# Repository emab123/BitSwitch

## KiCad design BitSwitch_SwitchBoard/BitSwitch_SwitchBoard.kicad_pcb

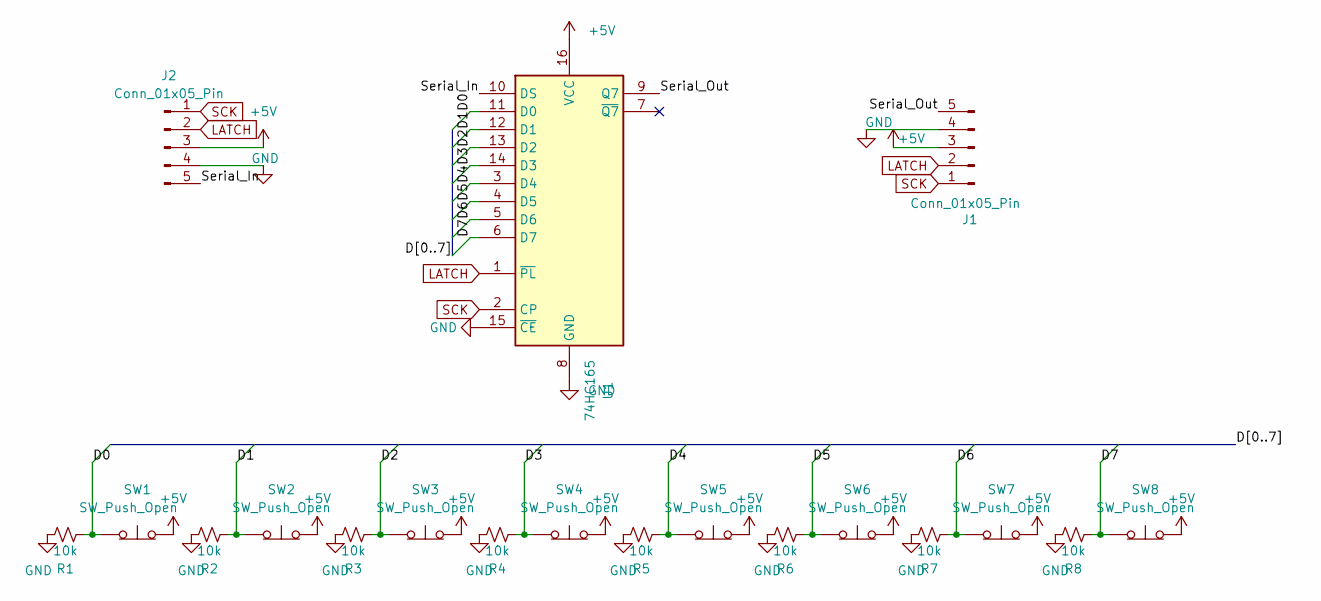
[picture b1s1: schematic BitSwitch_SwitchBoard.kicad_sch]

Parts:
J1, J2: Conn_01x05_Pin; JST_XH_B5B-XH-AM_1x05_P2.50mm_Vertical
R1, R2, R3, R4, R5, R6, R7, R8: 10k; R_0402_1005Metric
SW1, SW2, SW3, SW4, SW5, SW6, SW7, SW8: SW_Push_Open; SW-SMD_HX-KFC-V-105
U1: 74HC165; SOIC-16_3.9x9.9mm_P1.27mm

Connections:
+5V: J1.3, J2.3, SW1.2 (B), SW2.2 (B), SW3.2 (B), SW4.2 (B), SW5.2 (B), SW6.2 (B), SW7.2 (B), SW8.2 (B), U1.16 (VCC)
/D0: R1.2, SW1.1 (A), U1.11 (D0)
/D1: R2.2, SW2.1 (A), U1.12 (D1)
/D2: R3.2, SW3.1 (A), U1.13 (D2)
/D3: R4.2, SW4.1 (A), U1.14 (D3)
/D4: R5.2, SW5.1 (A), U1.3 (D4)
/D5: R6.2, SW6.1 (A), U1.4 (D5)
/D6: R7.2, SW7.1 (A), U1.5 (D6)
/D7: R8.2, SW8.1 (A), U1.6 (D7)
/Serial_In: J2.5, U1.10 (DS)
/Serial_Out: J1.5, U1.9 (Q7)
GND: J1.4, J2.4, R1.1, R2.1, R3.1, R4.1, R5.1, R6.1, R7.1, R8.1, U1.8 (GND), U1.15 (~CE)
LATCH: J1.2, J2.2, U1.1 (~PL)
SCK: J1.1, J2.1, U1.2 (CP)

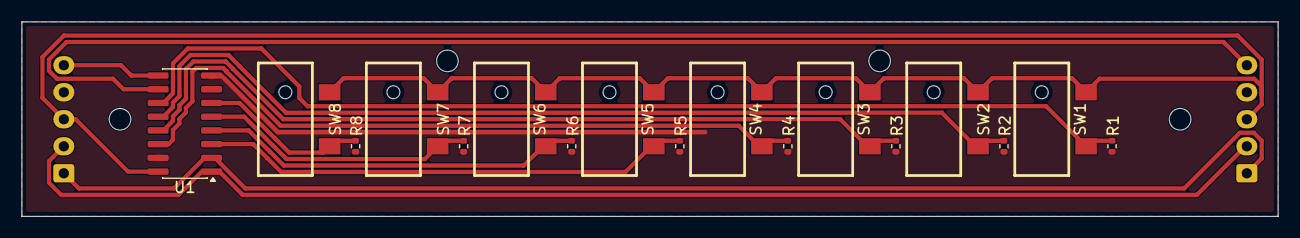
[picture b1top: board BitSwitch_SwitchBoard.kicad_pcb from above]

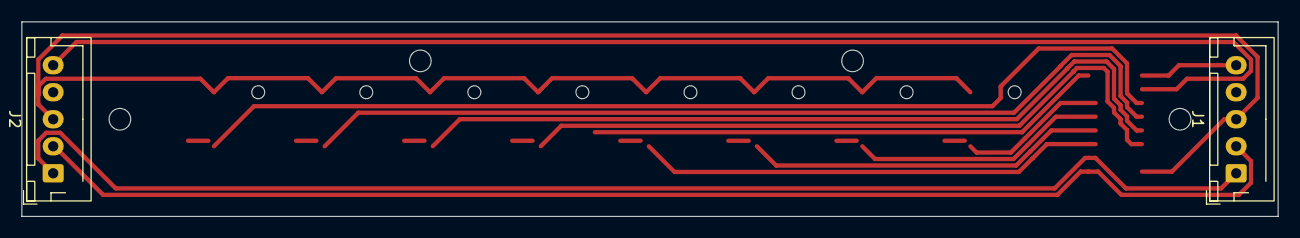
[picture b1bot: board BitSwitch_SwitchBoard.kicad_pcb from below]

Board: 2 copper layers, 116.2 x 18.0 mm, 23 parts (6 on the bottom side), 14 nets.

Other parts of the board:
HOLE1, HOLE2, HOLE3, HOLE4: MountingHole_2mm

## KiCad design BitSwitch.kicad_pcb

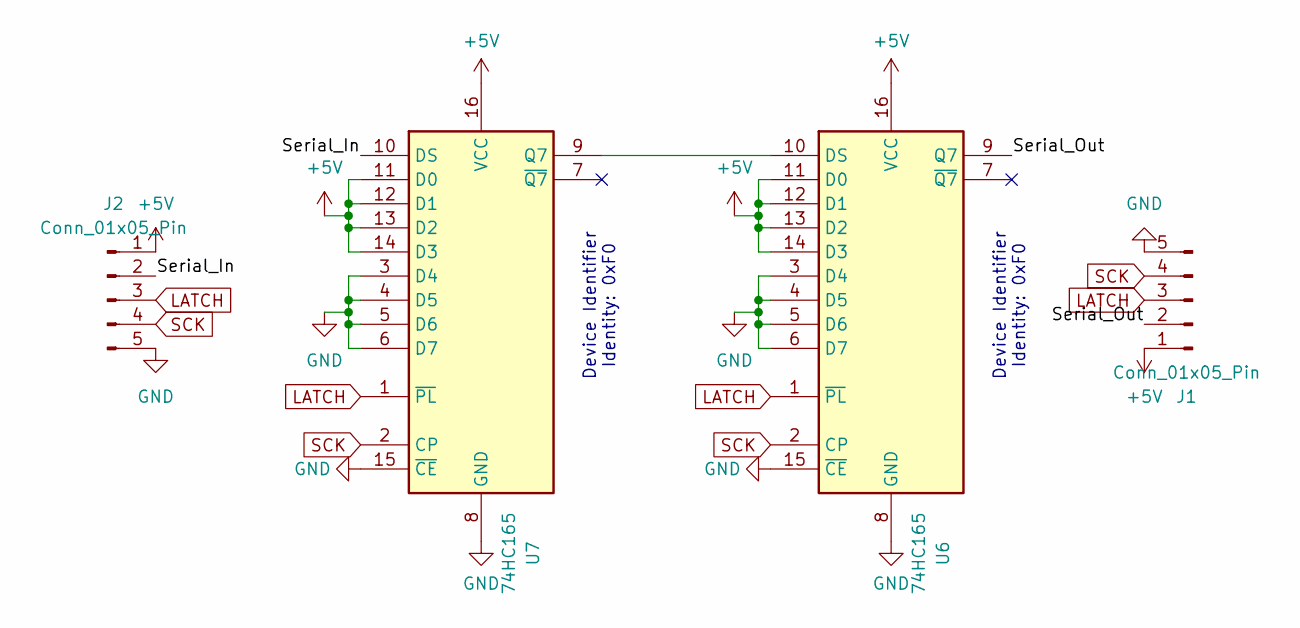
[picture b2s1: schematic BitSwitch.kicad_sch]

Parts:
J1, J2: Conn_01x05_Pin; JST_XH_B5B-XH-AM_1x05_P2.50mm_Vertical
U6, U7: 74HC165; SOIC-16_3.9x9.9mm_P1.27mm

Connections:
+5V: J1.1, J2.1, U6.11 (D0), U6.12 (D1), U6.13 (D2), U6.14 (D3), U6.16 (VCC), U7.11 (D0), U7.12 (D1), U7.13 (D2), U7.14 (D3), U7.16 (VCC)
/Serial_In: J2.2, U7.10 (DS)
/Serial_Out: J1.2, U6.9 (Q7)
GND: J1.5, J2.5, U6.3 (D4), U6.4 (D5), U6.5 (D6), U6.6 (D7), U6.8 (GND), U6.15 (~CE), U7.3 (D4), U7.4 (D5), U7.5 (D6), U7.6 (D7), U7.8 (GND), U7.15 (~CE)
LATCH: J1.3, J2.3, U6.1 (~PL), U7.1 (~PL)
unnamed: U6.10 (DS), U7.9 (Q7)
SCK: J1.4, J2.4, U6.2 (CP), U7.2 (CP)

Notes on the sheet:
Device Identifier Identity: 0xF0

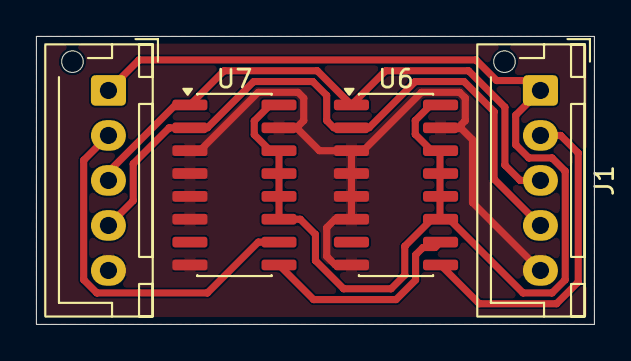
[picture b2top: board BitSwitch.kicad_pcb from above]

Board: 2 copper layers, 31.0 x 16.0 mm, 4 parts (0 on the bottom side), 7 nets.

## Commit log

2026-04-30 Add gcode generation
2026-04-30 Adjust board size
